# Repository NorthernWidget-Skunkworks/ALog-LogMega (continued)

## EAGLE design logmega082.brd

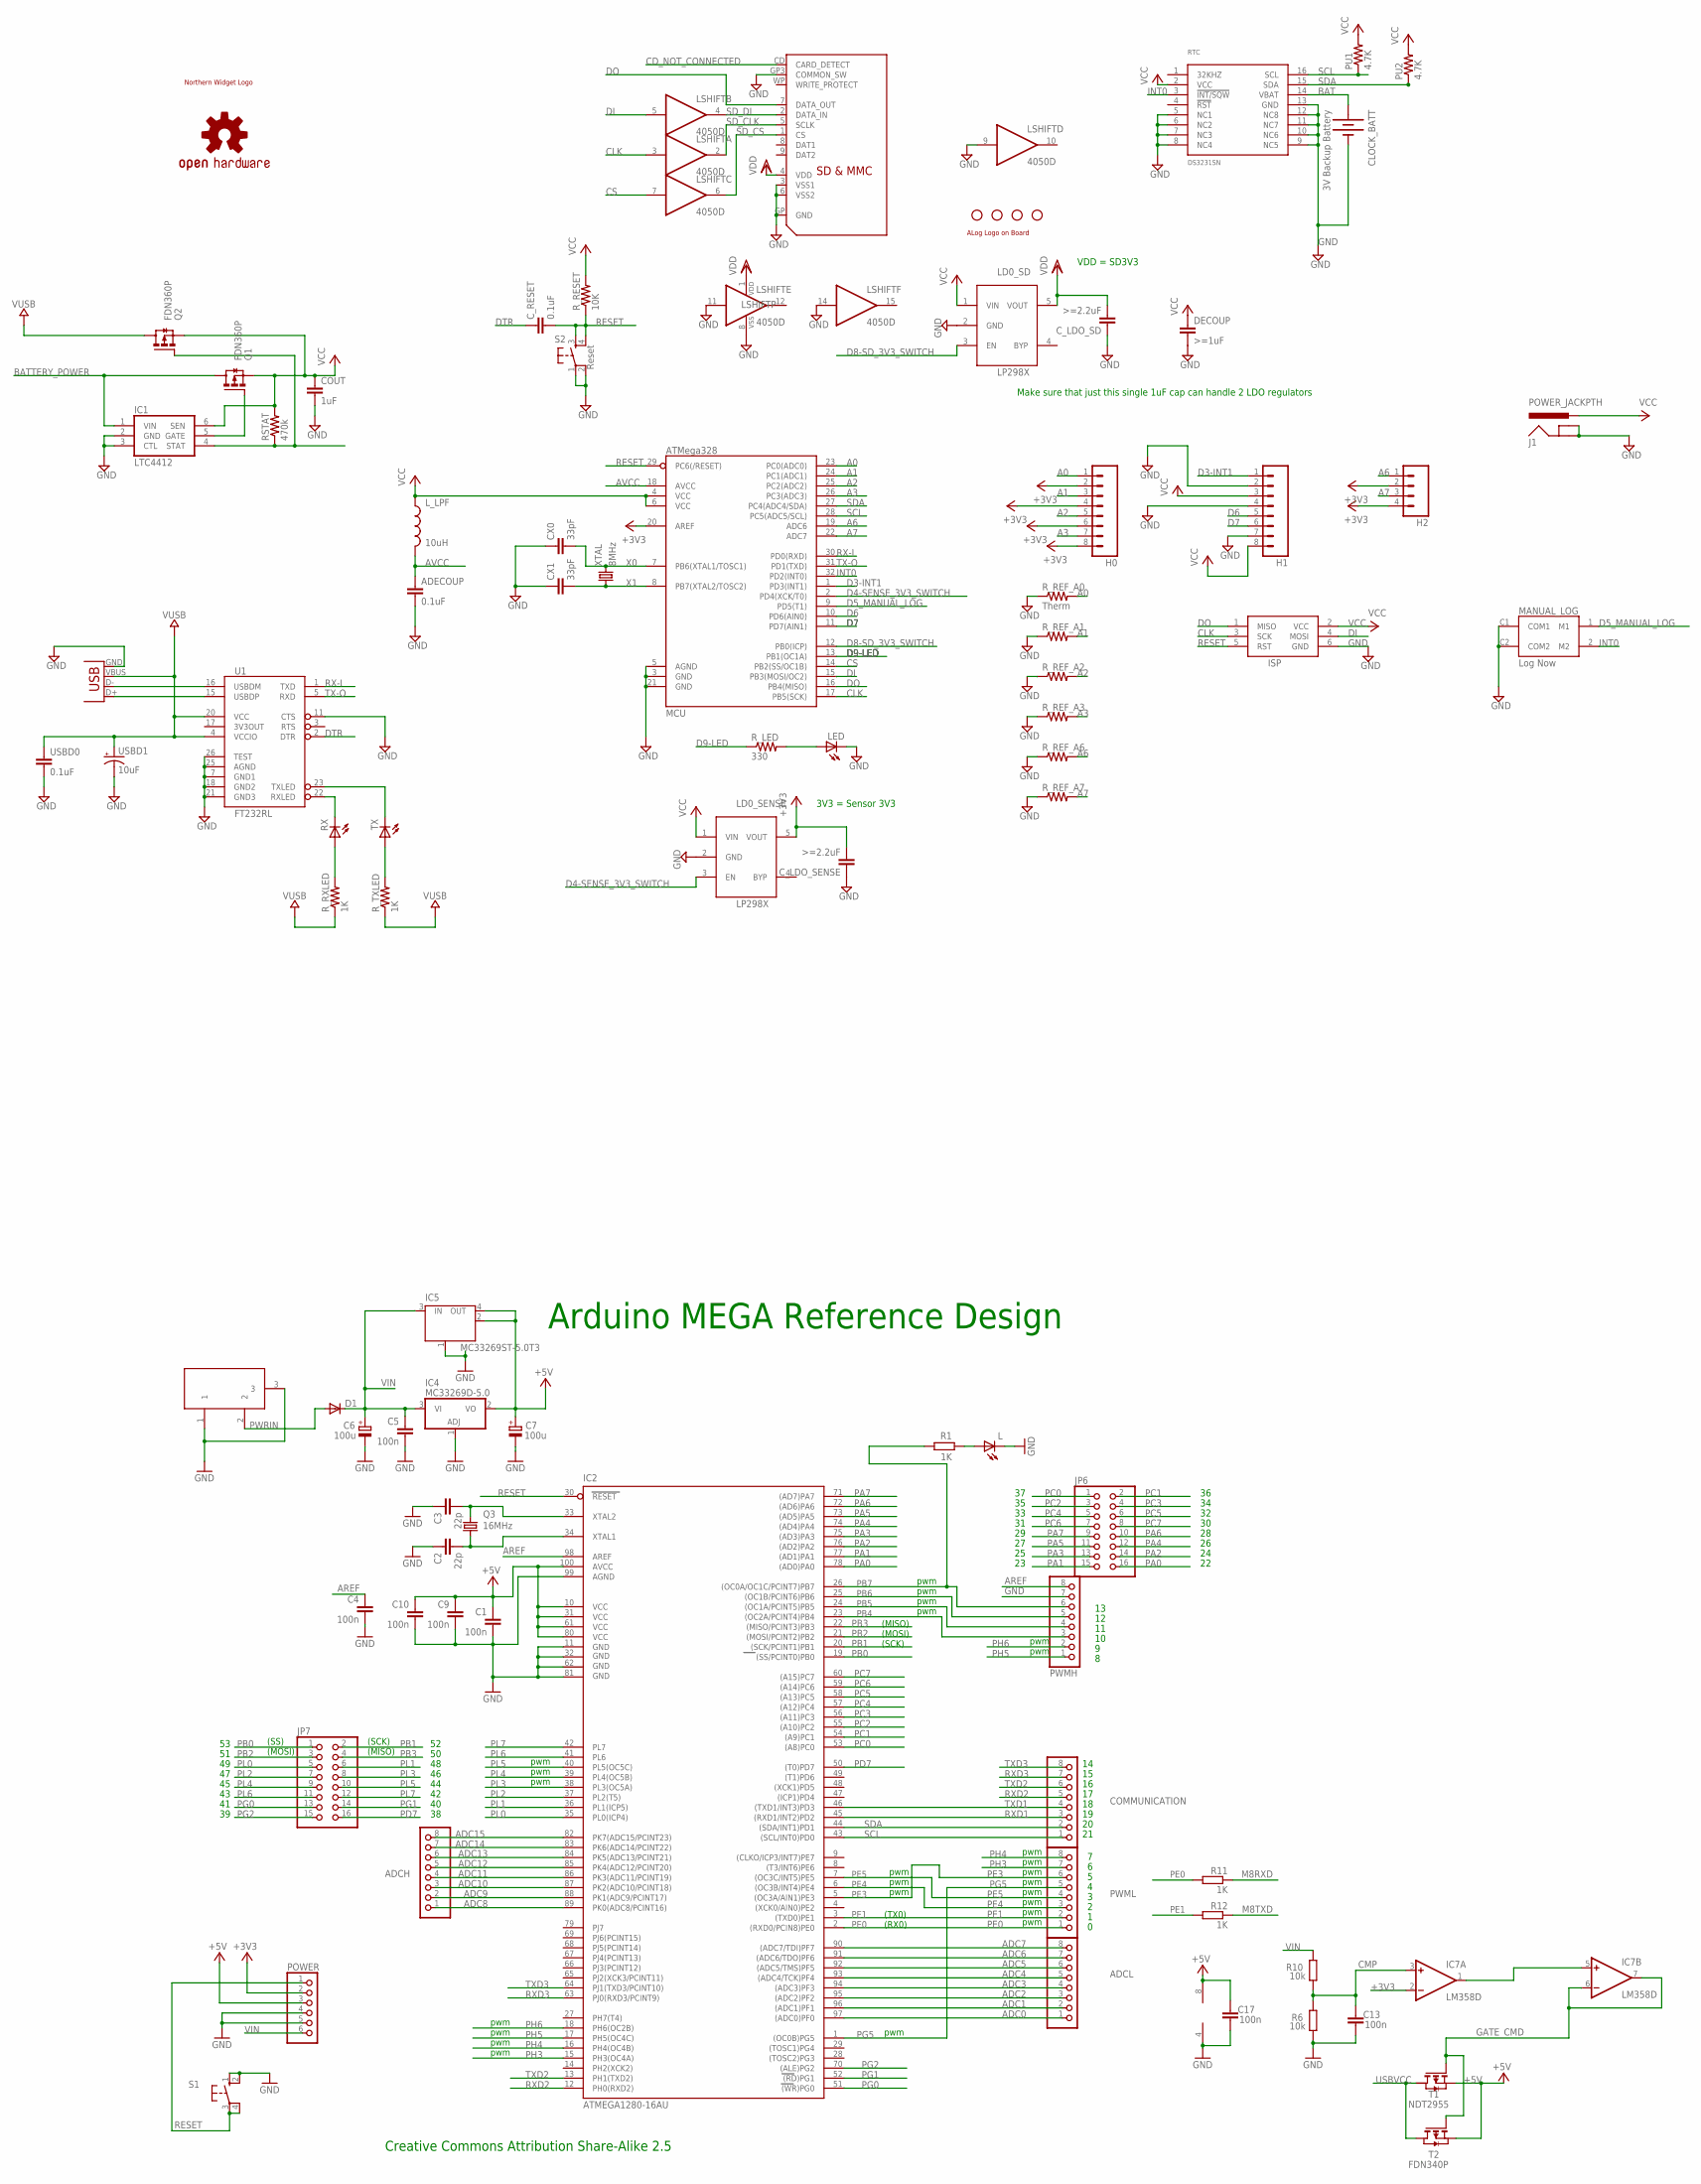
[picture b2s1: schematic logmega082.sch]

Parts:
ADCH: PINHD-1X8; 1X08
ADCL: PINHD-1X8; 1X08
ADECOUP: 0.1uF; C0603
C1, C4, C5, C9, C10, C13, C17: 100n; C0805RND
C2, C3: 22p; C0805RND
C6, C7: 100u; SMC_D
CLOCK_BATT: 3V Backup Battery; BATTCON_12MM_PTH
COMMUNICATION: PINHD-1X8; 1X08
COUT: 1uF; C0603-ROUND
CX0, CX1: 33pF; C0603
C_LDO_SD: >=2.2uF; C0603
C_LDO_SENSE: >=2.2uF; C0603
C_RESET: 0.1uF; C0603
D1: DIODE-SMB; SMB
DECOUP: >=1uF; C0603
H0, H1: M083.5MM-8; SCREWTERMINAL-3.5MM-8
H2: M04SCREW; SCREWTERMINAL-3.5MM-4
IC1: LTC4412; TSOT23-6
IC2: ATMEGA1280-16AU; TQFP100
IC4: MC33269D-5.0; DPACK
IC5: MC33269ST-5.0T3; SOT223
IC7: LM358D; SO08
ISP: AVRISP-6; AVRISP
J1: POWER_JACKPTH; POWER_JACK_PTH
JP1, JP2, JP3, JP4: STAND-OFF
JP5: USB-B; USB-B-PTH
JP6, JP7: PINHD-2X8; 2X08
L: LED0805ROUND; 0805RND
LD0_SD, LD0_SENSE: LP2985; SOT23-5L
LED: LED3MM
LOGO1: OSHW-LOGOM; OSHW-LOGO-M
LSHIFT: 4050D; SO16
L_LPF: 10uH; 0805
MANUAL_LOG: Log Now; TL_BUTTON
MCU: ATMega328; TQFP32-08
POWER: PINHD-1X6; 1X06
PU1, PU2: 4.7K; R0603@1
PWMH: PINHD-1X8; 1X08
PWML: PINHD-1X8; 1X08
Q1, Q2: FDN360P; SUPER-SOT3
Q3: 16MHz; HC49/S
R1: 1K; R0805RND
R6, R10: 10k; R0805RND
R11, R12: 1K; RCL_0805RND
RSTAT: 470k; R0603@1
RTC: DS3231SN; SO16W
RX: LED0603; LED-0603
R_LED: 330; R0603@1
R_REF_A0: Therm; 0207/10
R_REF_A1, R_REF_A2, R_REF_A3, R_REF_A6, R_REF_A7: R-US_0207/10; 0207/10
R_RESET: 10K; R0603@1
R_RXLED: 1K; R0603@1
R_TXLED: 1K; R0603@1
S1: 10-XX; B3F-10XX
S2: Reset; TACTILE_SWITCH_SMD
SD: SDMMC06132; 06132
T1: NDT2955; SOT223
T2: FDN340P; SOT-23
TX: LED0603; LED-0603
U1: FT232RL; SSOP28DB
U$1: NWLOGO
U$2: ALOG_LOGO_V1_5.5MM; ALOG_LOGO_V1_SMALL
USBD0: 0.1uF; C0603
USBD1: 10uF; EIA3216
X2: DC21MMX; DC-21MM
XTAL: 8MHz; HC49U-V

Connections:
+3V3: C_LDO_SENSE.2, H0.2, H0.4, H0.6, H0.8, H2.2, H2.4, IC7.2 (-IN), LD0_SENSE.5 (VOUT), MCU.20 (AREF), POWER.2
+5V: C1.1, C7.+, C9.1, C10.1, C17.2, IC2.10 (VCC), IC2.31 (VCC1), IC2.61 (VCC2), IC2.80 (VCC3), IC2.100 (AVCC), IC4.2 (VO), IC5.2 (OUT), IC5.4 (OUT), IC7.8 (V+), POWER.3, T1.3 (S), T2.2 (S)
A0: H0.1, MCU.23 (PC0(ADC0)), R_REF_A0.2
A1: H0.3, MCU.24 (PC1(ADC1)), R_REF_A1.2
A2: H0.5, MCU.25 (PC2(ADC2)), R_REF_A2.2
A3: H0.7, MCU.26 (PC3(ADC3)), R_REF_A3.2
A6: H2.1, MCU.19 (ADC6), R_REF_A6.2
A7: H2.3, MCU.22 (ADC7), R_REF_A7.2
ADC0: ADCL.1, IC2.97 ((ADC0)PF0)
ADC1: ADCL.2, IC2.96 ((ADC1)PF1)
ADC2: ADCL.3, IC2.95 ((ADC2)PF2)
ADC3: ADCL.4, IC2.94 ((ADC3)PF3)
ADC4: ADCL.5, IC2.93 ((ADC4/TCK)PF4)
ADC5: ADCL.6, IC2.92 ((ADC5/TMS)PF5)
ADC6: ADCL.7, IC2.91 ((ADC6/TDO)PF6)
ADC7: ADCL.8, IC2.90 ((ADC7/TDI)PF7)
ADC8: ADCH.1, IC2.89 (PK0(ADC8/PCINT16))
ADC9: ADCH.2, IC2.88 (PK1(ADC9/PCINT17))
ADC10: ADCH.3, IC2.87 (PK2(ADC10/PCINT18))
ADC11: ADCH.4, IC2.86 (PK3(ADC11/PCINT19))
ADC12: ADCH.5, IC2.85 (PK4(ADC12/PCINT20))
ADC13: ADCH.6, IC2.84 (PK5(ADC13/PCINT21))
ADC14: ADCH.7, IC2.83 (PK6(ADC14/PCINT22))
ADC15: ADCH.8, IC2.82 (PK7(ADC15/PCINT23))
AREF: C4.1, IC2.98 (AREF), PWMH.8
AVCC: ADECOUP.1, L_LPF.2, MCU.18 (AVCC)
BAT: CLOCK_BATT.VCC@1 (+), RTC.14 (VBAT)
BATTERY_POWER: IC1.1 (VIN), Q1.3 (D)
CD_NOT_CONNECTED: SD.CD (CARD_DETECT)
CLK: ISP.3 (SCK), LSHIFT.3 (I), MCU.17 (PB5(SCK))
CMP: C13.2, IC7.3 (+IN), R6.2, R10.1
CS: LSHIFT.7 (I), MCU.14 (PB2(SS/OC1B))
D3-INT1: H1.1, MCU.1 (PD3(INT1))
D4-SENSE_3V3_SWITCH: LD0_SENSE.3 (EN), MCU.2 (PD4(XCK/T0))
D5_MANUAL_LOG: MANUAL_LOG.1 (M1), MCU.9 (PD5(T1))
D6: H1.5, MCU.10 (PD6(AIN0))
D7: H1.6, MCU.11 (PD7(AIN1))
D8-SD_3V3_SWITCH: LD0_SD.3 (EN), MCU.12 (PB0(ICP))
D9-LED: MCU.13 (PB1(OC1A)), R_LED.1
DI: ISP.4 (MOSI), LSHIFT.5 (I), MCU.15 (PB3(MOSI/OC2))
DO: ISP.1 (MISO), MCU.16 (PB4(MISO)), SD.7 (DATA_OUT)
DTR: C_RESET.1, U1.2 (DTR)
GATE_CMD: IC7.6 (-IN), IC7.7 (OUT), T1.1 (G), T2.3 (G)
GND: ADECOUP.2, C1.2, C2.1, C3.1, C4.2, C5.2, C6.-, C7.-, C9.2, C10.2, C13.1, C17.1, CLOCK_BATT.GND (-), COUT.2, CX0.1, CX1.1, C_LDO_SD.1, C_LDO_SENSE.1, DECOUP.2, H1.2, H1.4, H1.7, IC1.2 (GND), IC1.3 (CTL), IC2.11 (GND), IC2.32 (GND1), IC2.62 (GND2), IC2.81 (GND3), IC2.99 (AGND), IC4.1 (ADJ), IC5.1 (GND/ADJ), IC7.4 (V-), ISP.6 (GND), J1.GND, J1.GNDBREAK, JP5.GND, L.P$2 (C), LD0_SD.2 (GND), LD0_SENSE.2 (GND), LED.K (C), LSHIFT.8 (VSS), LSHIFT.9 (I), LSHIFT.11 (I), LSHIFT.14 (I), MANUAL_LOG.C1 (COM1), MANUAL_LOG.C2 (COM2), MCU.3 (GND), MCU.5 (AGND), MCU.21 (GND), POWER.4, POWER.5, PWMH.7, R6.1, RTC.5 (NC1), RTC.6 (NC2), RTC.7 (NC3), RTC.8 (NC4), RTC.9 (NC5), RTC.10 (NC6), RTC.11 (NC7), RTC.12 (NC8), RTC.13 (GND), R_REF_A0.1, R_REF_A1.1, R_REF_A2.1, R_REF_A3.1, R_REF_A6.1, R_REF_A7.1, S1.1 (S), S1.2 (S1), S2.1, S2.2, SD.3 (VSS1), SD.6 (VSS2), SD.GP (GND), SD.GP3 (COMMON_SW), U1.7 (GND1), U1.11 (CTS), U1.18 (GND2), U1.21 (GND3), U1.25 (AGND), U1.26 (TEST), USBD0.2, USBD1.C (-), X2.1, X2.3
INT0: MANUAL_LOG.2 (M2), MCU.32 (PD2(INT0)), RTC.3 (!INT/SQW)
LED+: LED.A, R_LED.2
M8RXD: R11.P$1 (1)
M8TXD: R12.P$1 (1)
unnamed: RX.C, U1.22 (RXLED)
unnamed: JP5.D+, U1.15 (USBDP)
unnamed: JP5.D-, U1.16 (USBDM)
unnamed: TX.C, U1.23 (TXLED)
unnamed: RX.A, R_RXLED.2
unnamed: R_TXLED.2, TX.A
unnamed: IC1.4 (STAT), Q2.1 (G), RSTAT.1
unnamed: IC1.5 (GATE), Q1.1 (G)
unnamed: C2.2, IC2.34 (XTAL1), Q3.1
unnamed: C3.2, IC2.33 (XTAL2), Q3.2
unnamed: L.P$1 (A), R1.2
unnamed: IC7.1 (OUT), IC7.5 (+IN)
PA0: IC2.78 ((AD0)PA0), JP6.16
PA1: IC2.77 ((AD1)PA1), JP6.15
PA2: IC2.76 ((AD2)PA2), JP6.14
PA3: IC2.75 ((AD3)PA3), JP6.13
PA4: IC2.74 ((AD4)PA4), JP6.12
PA5: IC2.73 ((AD5)PA5), JP6.11
PA6: IC2.72 ((AD6)PA6), JP6.10
PA7: IC2.71 ((AD7)PA7), JP6.9
PB0: IC2.19 ((SS/PCINT0)PB0), JP7.1
PB1: IC2.20 ((SCK/PCINT1)PB1), JP7.2
PB2: IC2.21 ((MOSI/PCINT2)PB2), JP7.3
PB3: IC2.22 ((MISO/PCINT3)PB3), JP7.4
PB4: IC2.23 ((OC2A/PCINT4)PB4), PWMH.3
PB5: IC2.24 ((OC1A/PCINT5)PB5), PWMH.4
PB6: IC2.25 ((OC1B/PCINT6)PB6), PWMH.5
PB7: IC2.26 ((OC0A/OC1C/PCINT7)PB7), PWMH.6, R1.1
PC0: IC2.53 ((A8)PC0), JP6.1
PC1: IC2.54 ((A9)PC1), JP6.2
PC2: IC2.55 ((A10)PC2), JP6.3
PC3: IC2.56 ((A11)PC3), JP6.4
PC4: IC2.57 ((A12)PC4), JP6.5
PC5: IC2.58 ((A13)PC5), JP6.6
PC6: IC2.59 ((A14)PC6), JP6.7
PC7: IC2.60 ((A15)PC7), JP6.8
PD7: IC2.50 ((T0)PD7), JP7.16
PE0: IC2.2 ((RXD0/PCIN8)PE0), PWML.1, R11.P$2 (2)
PE1: IC2.3 ((TXD0)PE1), PWML.2, R12.P$2 (2)
PE3: IC2.5 ((OC3A/AIN1)PE3), PWML.6
PE4: IC2.6 ((OC3B/INT4)PE4), PWML.3
PE5: IC2.7 ((OC3C/INT5)PE5), PWML.4
PG0: IC2.51 ((WR)PG0), JP7.13
PG1: IC2.52 ((RD)PG1), JP7.14
PG2: IC2.70 ((ALE)PG2), JP7.15
PG5: IC2.1 ((OC0B)PG5), PWML.5
PH3: IC2.15 (PH3(OC4A)), PWML.7
PH4: IC2.16 (PH4(OC4B)), PWML.8
PH5: IC2.17 (PH5(OC4C)), PWMH.1
PH6: IC2.18 (PH6(OC2B)), PWMH.2
PL0: IC2.35 (PL0(ICP4)), JP7.5
PL1: IC2.36 (PL1(ICP5)), JP7.6
PL2: IC2.37 (PL2(T5)), JP7.7
PL3: IC2.38 (PL3(OC5A)), JP7.8
PL4: IC2.39 (PL4(OC5B)), JP7.9
PL5: IC2.40 (PL5(OC5C)), JP7.10
PL6: IC2.41 (PL6), JP7.11
PL7: IC2.42 (PL7), JP7.12
PWRIN: D1.A, X2.2
RESET: C_RESET.2, IC2.30 (RESET), ISP.5 (RST), MCU.29 (PC6(/RESET)), POWER.1, R_RESET.1, S1.3, S1.4 (P1), S2.3, S2.4
RX-I: MCU.30 (PD0(RXD)), U1.1 (TXD)
RXD1: COMMUNICATION.3, IC2.45 ((RXD1/INT2)PD2)
RXD2: COMMUNICATION.5, IC2.12 (PH0(RXD2))
RXD3: COMMUNICATION.7, IC2.63 (PJ0(RXD3/PCINT9))
SCL: COMMUNICATION.1, IC2.43 ((SCL/INT0)PD0), MCU.28 (PC5(ADC5/SCL)), PU1.1, RTC.16 (SCL)
SDA: COMMUNICATION.2, IC2.44 ((SDA/INT1)PD1), MCU.27 (PC4(ADC4/SDA)), PU2.1, RTC.15 (SDA)
SD_CLK: LSHIFT.2 (O), SD.5 (SCLK)
SD_CS: LSHIFT.6 (O), SD.1 (CS)
SD_DI: LSHIFT.4 (O), SD.2 (DATA_IN)
TX-O: MCU.31 (PD1(TXD)), U1.5 (RXD)
TXD1: COMMUNICATION.4, IC2.46 ((TXD1/INT3)PD3)
TXD2: COMMUNICATION.6, IC2.13 (PH1(TXD2))
TXD3: COMMUNICATION.8, IC2.64 (PJ1(TXD3/PCINT10))
USBVCC: T1.2 (D), T2.1 (D)
VCC: COUT.1, DECOUP.1, H1.3, H1.8, IC1.6 (SEN), ISP.2 (VCC), J1.PWR, LD0_SD.1 (VIN), LD0_SENSE.1 (VIN), L_LPF.1, MCU.4 (VCC), MCU.6 (VCC), PU1.2, PU2.2, Q1.2 (S), Q2.2 (S), RSTAT.2, RTC.2 (VCC), R_RESET.2
VDD: C_LDO_SD.2, LD0_SD.5 (VOUT), LSHIFT.1 (VDD), SD.4 (VDD)
VIN: C5.1, C6.+, D1.C, IC4.3 (VI), IC5.3 (IN), POWER.6, R10.2
VUSB: JP5.VBUS, Q2.3 (D), R_RXLED.1, R_TXLED.1, U1.4 (VCCIO), U1.20 (VCC), USBD0.1, USBD1.A (+)
X0: CX0.2, MCU.7 (PB6(XTAL1/TOSC1)), XTAL.2
X1: CX1.2, MCU.8 (PB7(XTAL2/TOSC2)), XTAL.1

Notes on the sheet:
VDD = SD3V3
3V3 = Sensor 3V3
Make sure that just this single 1uF cap can handle 2 LDO regulators
Arduino MEGA Reference Design
pwm
(TX0)
(RX0)
(MISO)
(SCK)
(MOSI)
(SS)
Creative Commons Attribution Share-Alike 2.5

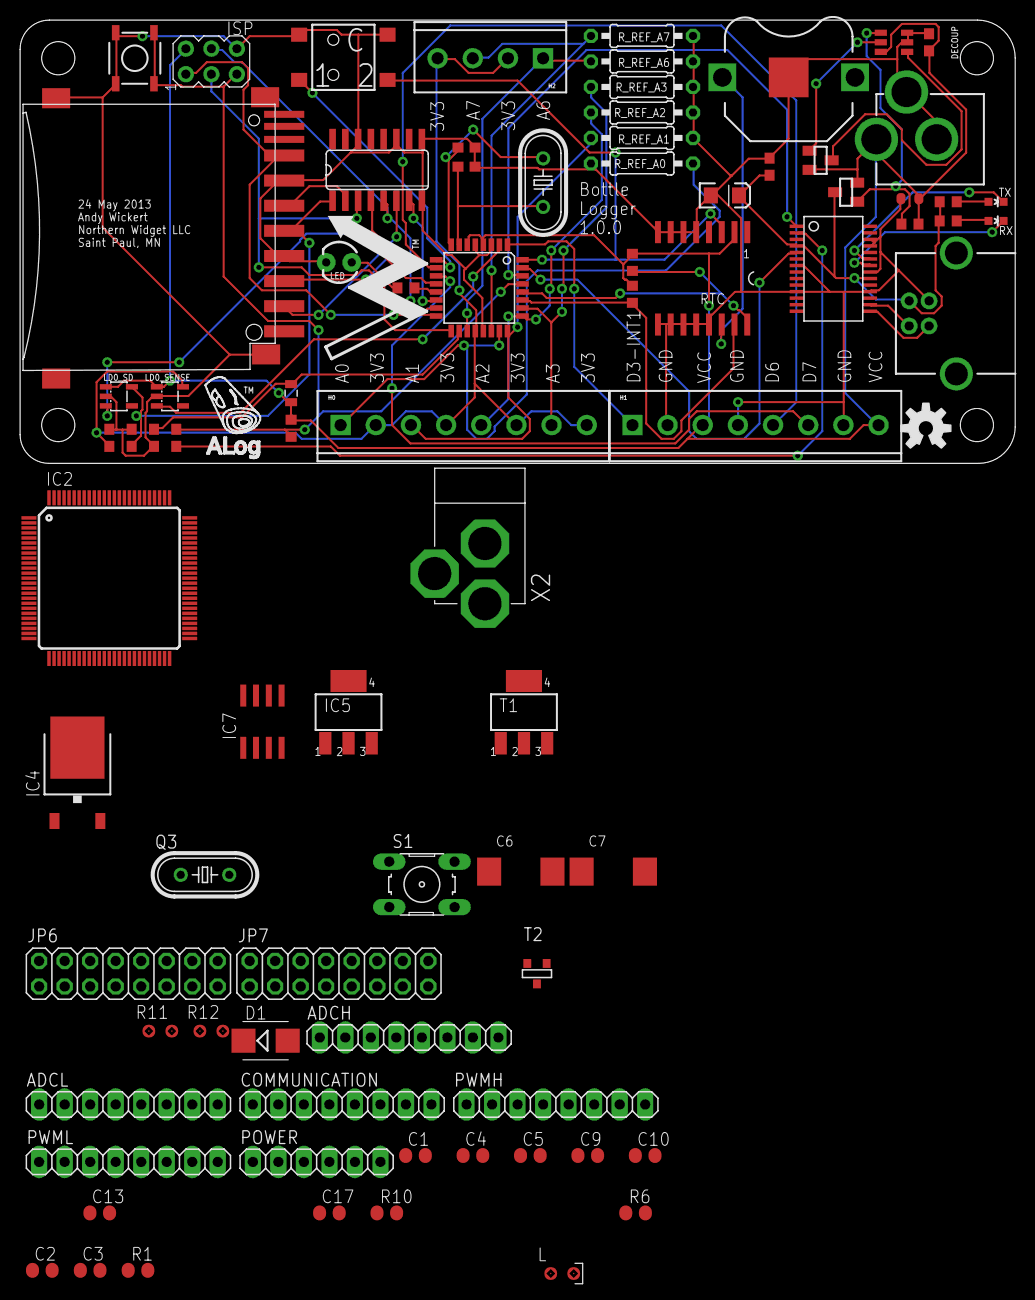
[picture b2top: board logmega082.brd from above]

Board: 2 copper layers, 99.0 x 44.1 mm, 89 parts (0 on the bottom side), 125 nets.

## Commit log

2013-09-11 Starting to splice together the ALog BottleLogger and Arduino Mega
2014-05-29 rmv datasheet for part that is not used
2014-05-29 Remove old v. 0.8.2
2014-05-29 Eagle CAD files and Gerbers
2014-05-29 DigiKey bill of materials
2014-05-30 Update to reflect current design parameters
2014-06-03 Scale drawing PDF of board
2014-06-12 begin 083_rev2
2014-06-12 Update README.md
    add notes about what is out of date w/ current revision work.
2014-06-13 Load switch resistors and capacitors labeled (#11) and CR2032 replaced with part with keepout (#3)
2014-06-13 Moved 'Log Now' and 'Reset' buttons (Issue #1)
2014-06-16 Multiple silkscreen and value label changes: #13 #16 #18 #20
2018-06-17 CC-BY-SA 4.0
2018-06-17 CC-BY-SA update to 4.0
2018-06-17 See if header is noted by GitHub
2018-06-17 does this header work?
2018-06-17 Update LICENSE
